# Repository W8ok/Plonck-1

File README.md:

# The Plonck-1 Computer

A silly goofy little 1-bit computer that im writing an emulator for.  
And also my first ever C project and the goal isnt to make the best thing ever, but to just to get used to the C syntax.  
  
Inspired by the MC14500 ICU and Usagi Electric's 24 vacuum tube SBC variant.  
https://github.com/Nakazoto/UE-0.1/tree/main  

## Architecture
LU integrated into instruction decoder  
Arbitrary expandable ROM/RAM just like the MC14500.  
Data is almost always equal to memory or input.  
Machine code is written in the format: DOOOAAAA, where D is Data, O is opcode and A is address.  

**Look at the included .asm files for example assembly code and syntax.**  
To assemble a program, pipe your .asm file into the assembler.py,  
In Linux, cd into the programs directory and do: `cat test.asm | assembler.py`  
this will create a hexfile in the emulator directory.  
The computer will execute it automatically, so long as you dont somehow, for some reason write a program more than 64kB large.  
To run the computer enter the emulator directory and run: `make run` and watch it go at a default of 10Hz.  
At the end of every program please use the function "**HALT**", this tells the computer to halt and output its memory content.  

## ISA
|**Opcode**|**Mnemonic**|**Operation**|**Notes**
|:---:|:---|:---|:---|
|`000`|**AND**|`Data AND ACC → ACC`||
|`001`|**XNOR**|`Data XNOR ACC → ACC`||
|`010`|**NOP**|`No Operation`||
|`011`|**ORCD**|`NOT(Data) OR ACC → ACC`||
|`100`|**LD**|`Data → ACC`||
|`101`|**ORCR**|`Data OR NOT(ACC) → ACC`||
|`110`|**OR**|`Data OR ACC → ACC`||
|`111`|**STO**|`ACC → Memory`|If the Data signal is also high it results in a Halt operation|

## Languages
C  
Python  
Custom Assembly / Machine Code  

## Status
ISA - Finished  
Emulator - Finished prototype  
Assembler - Finished prototype

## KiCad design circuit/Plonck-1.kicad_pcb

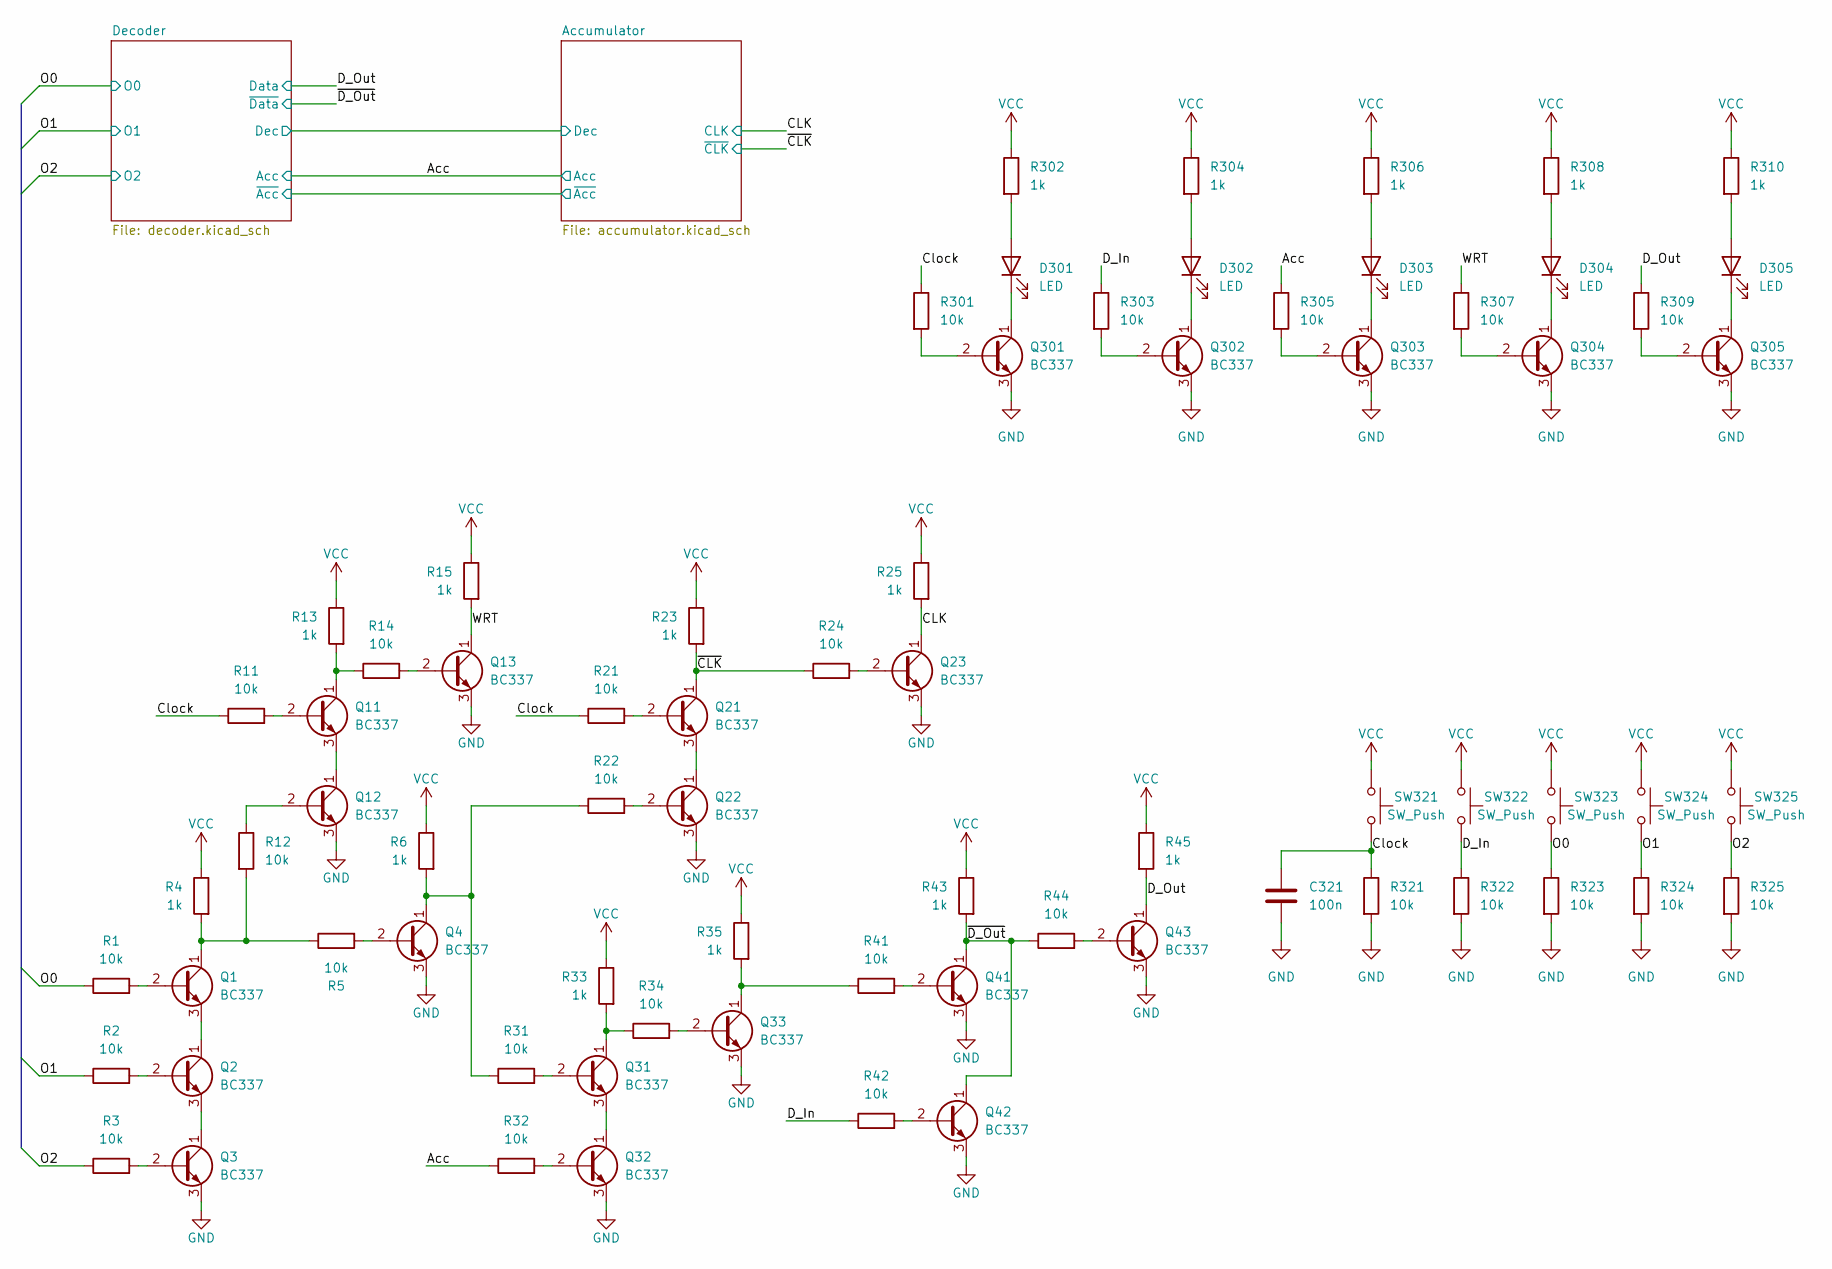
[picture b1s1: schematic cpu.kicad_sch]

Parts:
C321: 100n; C_Disc_D5.0mm_W2.5mm_P5.00mm
D301, D302, D303, D304, D305: LED; LED_D5.0mm
Q1, Q2, Q3, Q4, Q11, Q12, Q13, Q21, Q22, Q23, Q31, Q32, Q33, Q41, Q42, Q43, Q301, Q302, Q303, Q304, Q305: BC337; TO-92_Inline
R1, R2, R3, R5, R11, R12, R14, R21, R22, R24, R31, R32, R34, R41, R42, R44, R301, R303, R305, R307, R309, R321, R322, R323, R324, R325: 10k; R_Axial_DIN0207_L6.3mm_D2.5mm_P10.16mm_Horizontal
R4, R6, R13, R15, R23, R25, R33, R35, R43, R45, R302, R304, R306, R308, R310: 1k; R_Axial_DIN0207_L6.3mm_D2.5mm_P10.16mm_Horizontal
SW321, SW322, SW323, SW324, SW325: SW_Push; SW_PUSH_6mm

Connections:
/CPU/Acc: R32.1, R305.1; also elsewhere on the board
/CPU/CLK: Q23.1 (C), R25.2; also elsewhere on the board
/CPU/Clock: C321.1, R11.1, R21.1, R301.1, R321.1, SW321.2
/CPU/D_In: R42.1, R303.1, R322.1, SW322.2
/CPU/D_Out: Q43.1 (C), R45.2, R309.1; also elsewhere on the board
/CPU/O0: R1.1, R323.1, SW323.2; also elsewhere on the board
/CPU/O1: R2.1, R324.1, SW324.2; also elsewhere on the board
/CPU/O2: R3.1, R325.1, SW325.2; also elsewhere on the board
/CPU/WRT: Q13.1 (C), R15.2, R307.1
/CPU/~CLK: Q21.1 (C), R23.2, R24.1; also elsewhere on the board
/CPU/~D_Out: Q41.1 (C), Q42.1 (C), R43.2, R44.1; also elsewhere on the board
GND: C321.2, Q3.3 (E), Q4.3 (E), Q12.3 (E), Q13.3 (E), Q22.3 (E), Q23.3 (E), Q32.3 (E), Q33.3 (E), Q41.3 (E), Q42.3 (E), Q43.3 (E), Q301.3 (E), Q302.3 (E), Q303.3 (E), Q304.3 (E), Q305.3 (E), R321.2, R322.2, R323.2, R324.2, R325.2; also elsewhere on the board
unnamed: D301.2 (A), R302.2
unnamed: D301.1 (K), Q301.1 (C)
unnamed: D302.2 (A), R304.2
unnamed: D302.1 (K), Q302.1 (C)
unnamed: D303.2 (A), R306.2
unnamed: D303.1 (K), Q303.1 (C)
unnamed: D304.2 (A), R308.2
unnamed: D304.1 (K), Q304.1 (C)
unnamed: D305.2 (A), R310.2
unnamed: D305.1 (K), Q305.1 (C)
unnamed: Q1.2 (B), R1.2
unnamed: Q1.1 (C), R4.2, R5.1, R12.2
unnamed: Q1.3 (E), Q2.1 (C)
unnamed: Q2.2 (B), R2.2
unnamed: Q2.3 (E), Q3.1 (C)
unnamed: Q3.2 (B), R3.2
unnamed: Q4.2 (B), R5.2
unnamed: Q4.1 (C), R6.2, R22.1, R31.1
unnamed: Q11.2 (B), R11.2
unnamed: Q11.1 (C), R13.2, R14.1
unnamed: Q11.3 (E), Q12.1 (C)
unnamed: Q12.2 (B), R12.1
unnamed: Q13.2 (B), R14.2
unnamed: Q21.2 (B), R21.2
unnamed: Q21.3 (E), Q22.1 (C)
unnamed: Q22.2 (B), R22.2
unnamed: Q23.2 (B), R24.2
unnamed: Q31.2 (B), R31.2
unnamed: Q31.1 (C), R33.2, R34.1
unnamed: Q31.3 (E), Q32.1 (C)
unnamed: Q32.2 (B), R32.2
unnamed: Q33.2 (B), R34.2
unnamed: Q33.1 (C), R35.2, R41.1
unnamed: Q41.2 (B), R41.2
unnamed: Q42.2 (B), R42.2
unnamed: Q43.2 (B), R44.2
unnamed: Q301.2 (B), R301.2
unnamed: Q302.2 (B), R303.2
unnamed: Q303.2 (B), R305.2
unnamed: Q304.2 (B), R307.2
unnamed: Q305.2 (B), R309.2
VCC: R4.1, R6.1, R13.1, R15.1, R23.1, R25.1, R33.1, R35.1, R43.1, R45.1, R302.1, R304.1, R306.1, R308.1, R310.1, SW321.1, SW322.1, SW323.1, SW324.1, SW325.1; also elsewhere on the board

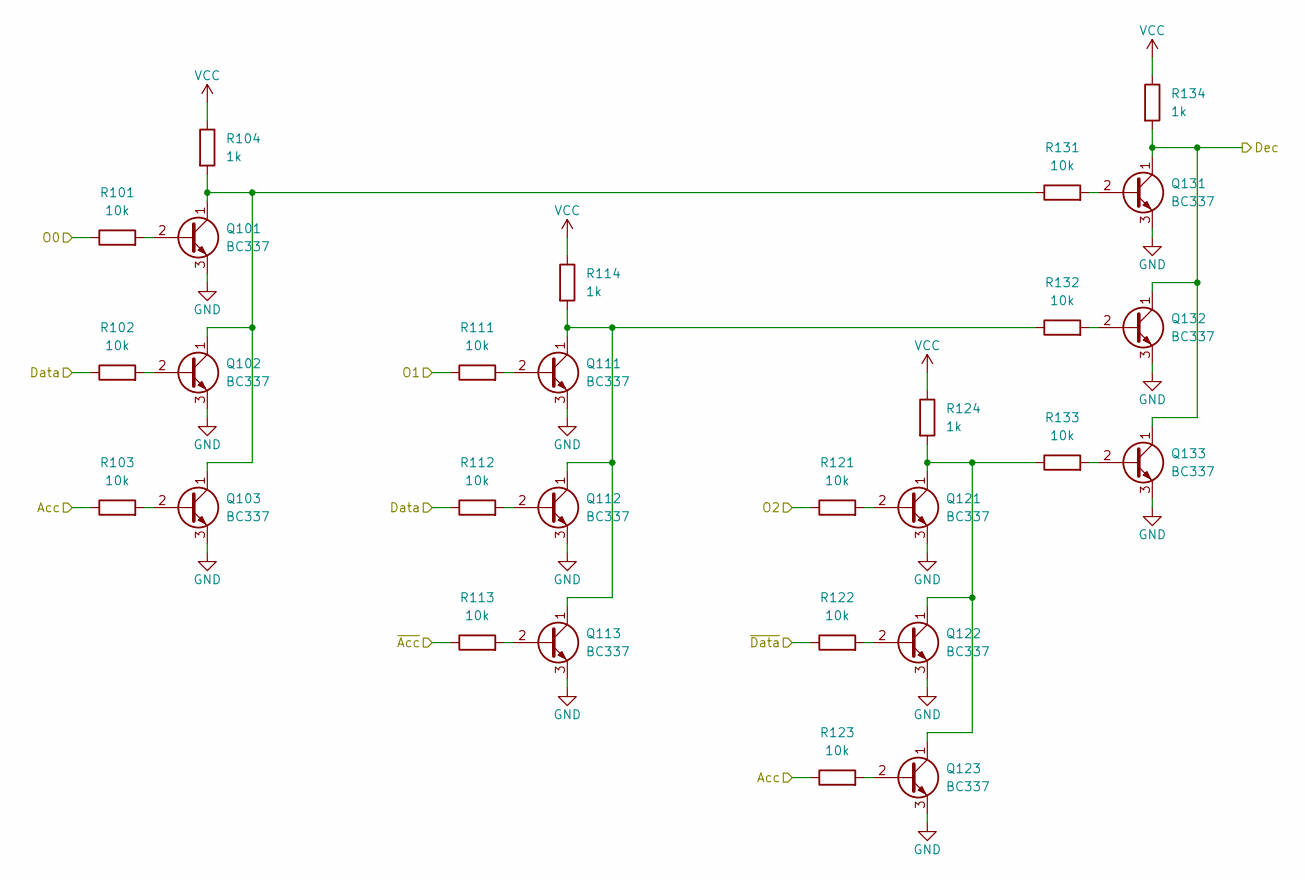
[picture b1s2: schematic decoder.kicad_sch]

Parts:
Q101, Q102, Q103, Q111, Q112, Q113, Q121, Q122, Q123, Q131, Q132, Q133: BC337; TO-92_Inline
R101, R102, R103, R111, R112, R113, R121, R122, R123, R131, R132, R133: 10k; R_Axial_DIN0207_L6.3mm_D2.5mm_P10.16mm_Horizontal
R104, R114, R124, R134: 1k; R_Axial_DIN0207_L6.3mm_D2.5mm_P10.16mm_Horizontal

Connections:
/CPU/Acc: R103.1, R123.1; also elsewhere on the board
/CPU/Accumulator/Dec: Q131.1 (C), Q132.1 (C), Q133.1 (C), R134.2; also elsewhere on the board
/CPU/Accumulator/~Acc: R113.1; also elsewhere on the board
/CPU/D_Out: R102.1, R112.1; also elsewhere on the board
/CPU/O0: R101.1; also elsewhere on the board
/CPU/O1: R111.1; also elsewhere on the board
/CPU/O2: R121.1; also elsewhere on the board
/CPU/~D_Out: R122.1; also elsewhere on the board
GND: Q101.3 (E), Q102.3 (E), Q103.3 (E), Q111.3 (E), Q112.3 (E), Q113.3 (E), Q121.3 (E), Q122.3 (E), Q123.3 (E), Q131.3 (E), Q132.3 (E), Q133.3 (E); also elsewhere on the board
unnamed: Q101.2 (B), R101.2
unnamed: Q101.1 (C), Q102.1 (C), Q103.1 (C), R104.2, R131.1
unnamed: Q102.2 (B), R102.2
unnamed: Q103.2 (B), R103.2
unnamed: Q111.2 (B), R111.2
unnamed: Q111.1 (C), Q112.1 (C), Q113.1 (C), R114.2, R132.1
unnamed: Q112.2 (B), R112.2
unnamed: Q113.2 (B), R113.2
unnamed: Q121.2 (B), R121.2
unnamed: Q121.1 (C), Q122.1 (C), Q123.1 (C), R124.2, R133.1
unnamed: Q122.2 (B), R122.2
unnamed: Q123.2 (B), R123.2
unnamed: Q131.2 (B), R131.2
unnamed: Q132.2 (B), R132.2
unnamed: Q133.2 (B), R133.2
VCC: R104.1, R114.1, R124.1, R134.1; also elsewhere on the board

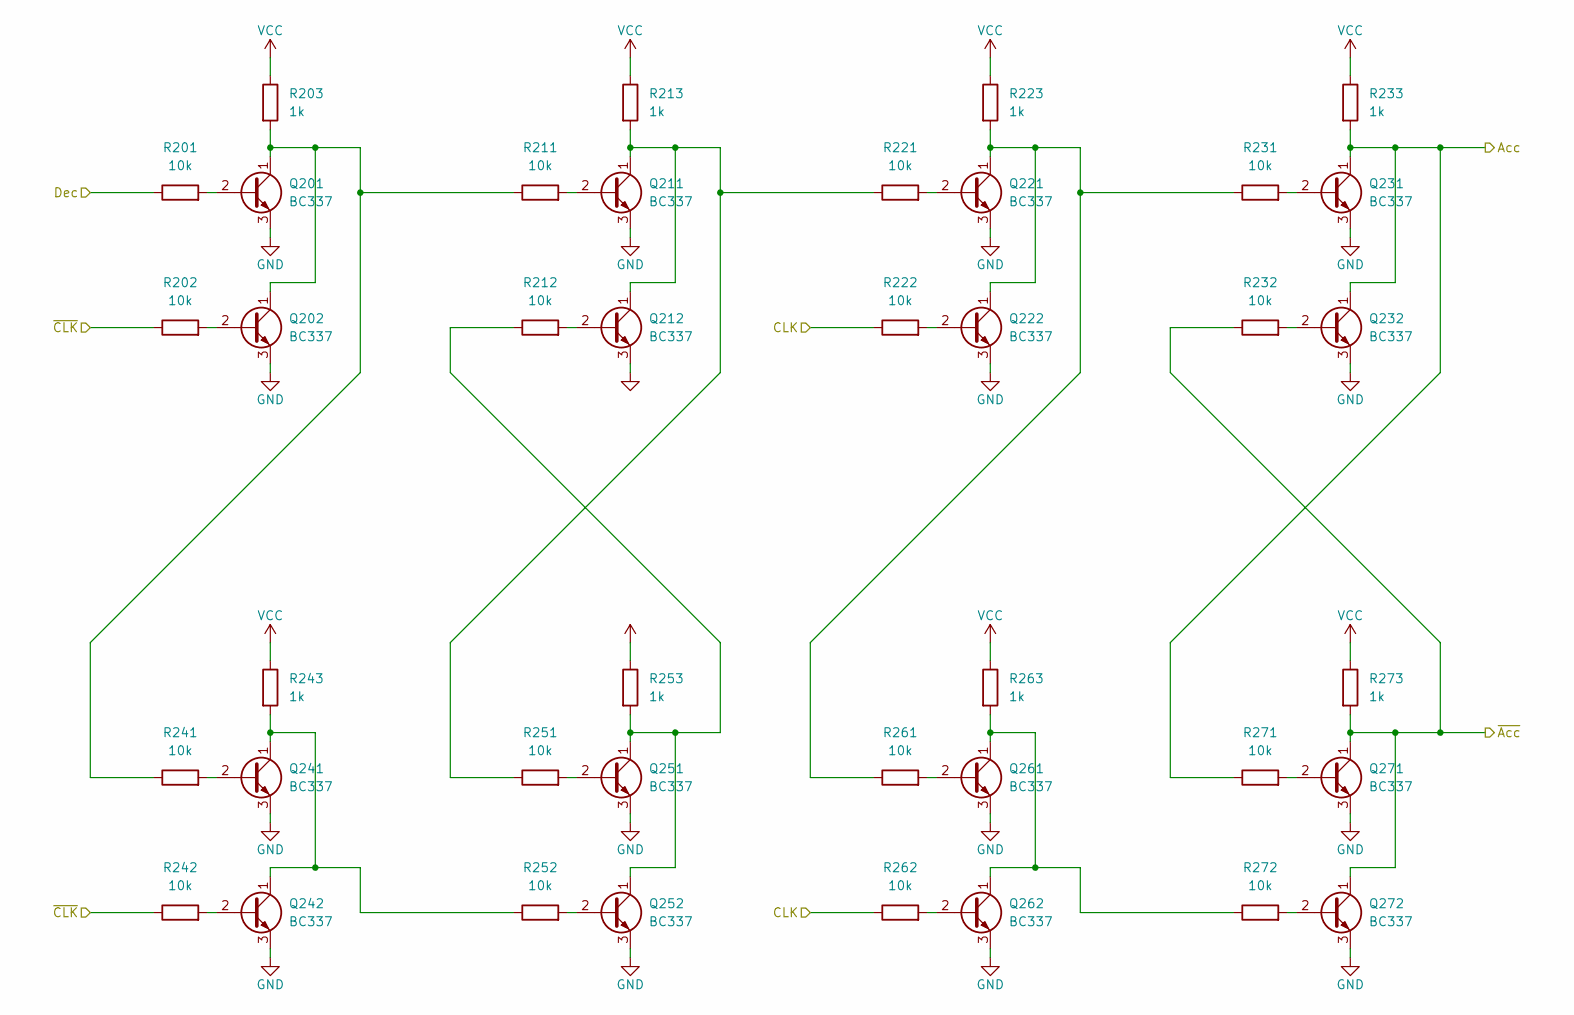
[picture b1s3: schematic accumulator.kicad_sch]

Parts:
Q201, Q202, Q211, Q212, Q221, Q222, Q231, Q232, Q241, Q242, Q251, Q252, Q261, Q262, Q271, Q272: BC337; TO-92_Inline
R201, R202, R211, R212, R221, R222, R231, R232, R241, R242, R251, R252, R261, R262, R271, R272: 10k; R_Axial_DIN0207_L6.3mm_D2.5mm_P10.16mm_Horizontal
R203, R213, R223, R233, R243, R253, R263, R273: 1k; R_Axial_DIN0207_L6.3mm_D2.5mm_P10.16mm_Horizontal

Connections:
/CPU/Acc: Q231.1 (C), Q232.1 (C), R233.2, R271.1; also elsewhere on the board
/CPU/Accumulator/Dec: R201.1; also elsewhere on the board
/CPU/Accumulator/~Acc: Q271.1 (C), Q272.1 (C), R232.1, R273.2; also elsewhere on the board
/CPU/CLK: R222.1, R262.1; also elsewhere on the board
/CPU/~CLK: R202.1, R242.1; also elsewhere on the board
GND: Q201.3 (E), Q202.3 (E), Q211.3 (E), Q212.3 (E), Q221.3 (E), Q222.3 (E), Q231.3 (E), Q232.3 (E), Q241.3 (E), Q242.3 (E), Q251.3 (E), Q252.3 (E), Q261.3 (E), Q262.3 (E), Q271.3 (E), Q272.3 (E); also elsewhere on the board
unnamed: Q201.2 (B), R201.2
unnamed: Q201.1 (C), Q202.1 (C), R203.2, R211.1, R241.1
unnamed: Q202.2 (B), R202.2
unnamed: Q211.2 (B), R211.2
unnamed: Q211.1 (C), Q212.1 (C), R213.2, R221.1, R251.1
unnamed: Q212.2 (B), R212.2
unnamed: Q221.2 (B), R221.2
unnamed: Q221.1 (C), Q222.1 (C), R223.2, R231.1, R261.1
unnamed: Q222.2 (B), R222.2
unnamed: Q231.2 (B), R231.2
unnamed: Q232.2 (B), R232.2
unnamed: Q241.2 (B), R241.2
unnamed: Q241.1 (C), Q242.1 (C), R243.2, R252.1
unnamed: Q242.2 (B), R242.2
unnamed: Q251.2 (B), R251.2
unnamed: Q251.1 (C), Q252.1 (C), R212.1, R253.2
unnamed: Q252.2 (B), R252.2
unnamed: Q261.2 (B), R261.2
unnamed: Q261.1 (C), Q262.1 (C), R263.2, R272.1
unnamed: Q262.2 (B), R262.2
unnamed: Q271.2 (B), R271.2
unnamed: Q272.2 (B), R272.2
VCC: R203.1, R213.1, R223.1, R233.1, R243.1, R253.1, R263.1, R273.1; also elsewhere on the board

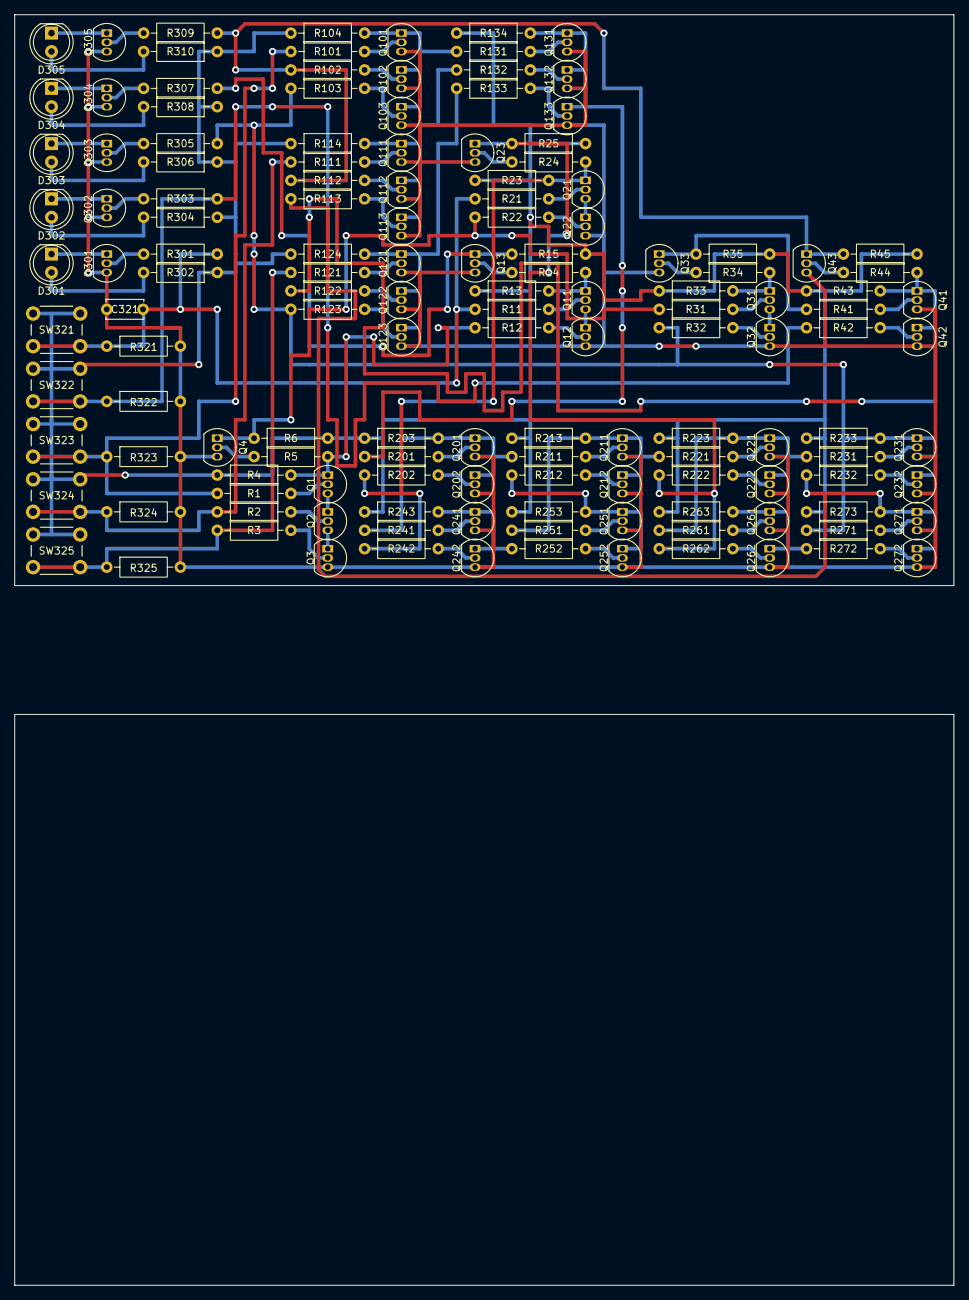
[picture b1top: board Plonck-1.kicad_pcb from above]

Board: 2 copper layers, 129.5 x 78.7 mm, 141 parts (0 on the bottom side), 93 nets.

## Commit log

2025-12-28 Second first commit
2025-12-28 README update
2025-12-29 Begun circuit design and emulation
2025-12-30 Finished early basic version of the emulator while also removing the circuit design to not overwhelm myself too quickly.
2026-01-01 Small fixes and cleanup
2026-01-01 Added a very bad but functional assembler and changed how the ROM is works as it now accesses a hexfile produced by the assembler.
2026-01-02 Updated README.md to accommodate for the assembler addition.
2026-01-04 Added a quick and dirty circuit for my TTL build of it
